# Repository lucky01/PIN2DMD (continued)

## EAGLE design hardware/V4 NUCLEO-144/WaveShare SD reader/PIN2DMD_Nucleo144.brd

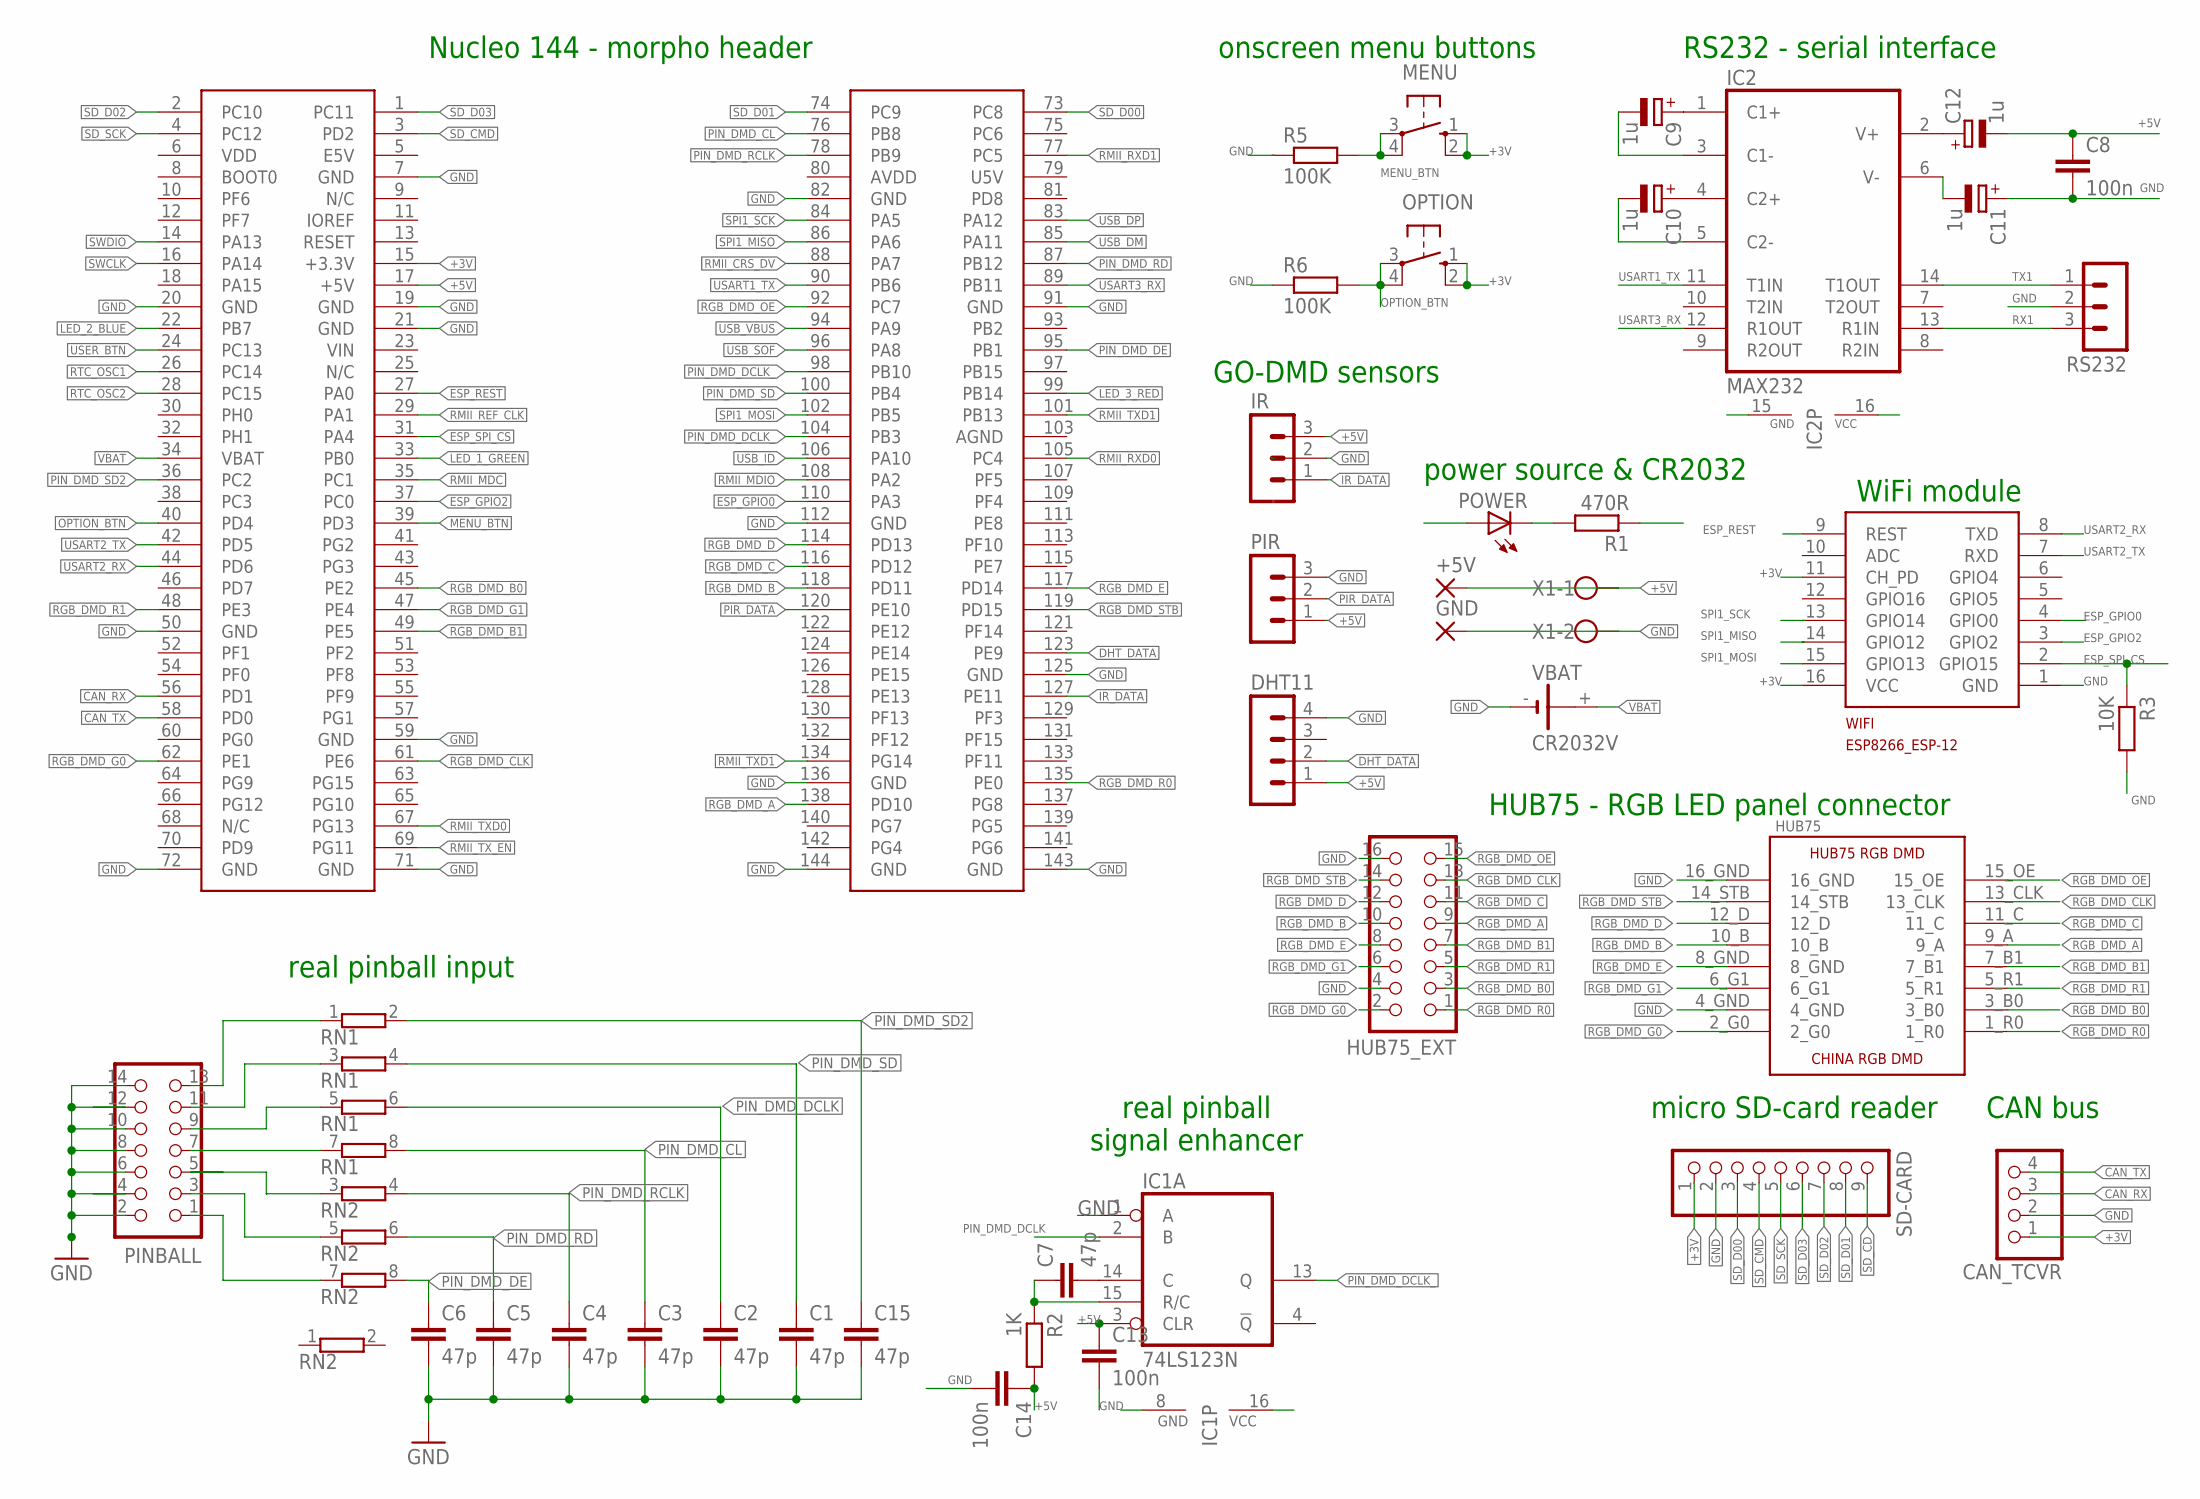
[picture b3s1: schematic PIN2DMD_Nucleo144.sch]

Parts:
+5V: WIREPADSMD2,54-5,08; SMD2,54-5,08
C1, C2, C3, C4, C5, C6, C7, C15: 47p; C025-024X044
C8, C13, C14: 100n; C025-024X044
C9, C10, C11, C12: 1u; E2-4
CAN_TCVR: PINHD-1X4; 1X04
DHT11: MA04-1
GND: WIREPADSMD2,54-5,08; SMD2,54-5,08
HUB75: RGB_DMD_HUB75_HEADER_FEMALE; 16_PIN_HUB75_RGB_FEMALE_DOWN
HUB75_EXT: CON_HEADER_2X08B; PINSHRD_PTH_2X08
IC1: 74LS123N; DIL16
IC2: MAX232; DIL16
IR: MA03-1
MENU: 10-XX; B3F-10XX
OPTION: 10-XX; B3F-10XX
PINBALL: CON_HEADER_2X07-PTH-SHROUDED; PINSHRD_PTH_2X07
PIR: MA03-1
POWER: LED3MM
R1: 470R; 0207/10
R2: 1K; 0207/10
R3: 10K; 0207/10
R5, R6: 100K; 0207/10
RN1, RN2: E4RP; SIL8
RS232: MA03-1
SD-CARD: PINHD-1X9; 1X09
U$1: NUCLEO-144
VBAT: CR2032V
WIFI: ESP8266_ESP-12; ESP8266-ESP12
X1: W237-102

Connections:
+3V: CAN_TCVR.1, MENU.1 (S), MENU.2 (S1), OPTION.1 (S), OPTION.2 (S1), SD-CARD.1, U$1.15 (+3.3V), WIFI.11 (CH_PD), WIFI.16 (VCC)
+5V: +5V.1, C8.1, C12.-, C13.1, C14.1, DHT11.1, IC1.3 (CLR), IC1.16 (VCC), IC2.16 (VCC), IR.3, PIR.1, POWER.A, R2.2, U$1.17 (+5V), X1.1
CAN_RX: CAN_TCVR.3, U$1.56 (PD1)
CAN_TX: CAN_TCVR.4, U$1.58 (PD0)
DHT_DATA: DHT11.2, U$1.123 (PE9)
ESP_GPIO0: U$1.110 (PA3), WIFI.4 (GPIO0)
ESP_GPIO2: U$1.37 (PC0), WIFI.3 (GPIO2)
ESP_REST: U$1.27 (PA0), WIFI.9 (REST)
ESP_SPI_CS: R3.1, U$1.31 (PA4), WIFI.2 (GPIO15)
GND: C1.2, C2.2, C3.2, C4.2, C5.2, C6.2, C8.2, C11.+, C13.2, C14.2, C15.2, CAN_TCVR.2, DHT11.4, GND.1, HUB75.4_GND, HUB75.16_GND, HUB75_EXT.4, HUB75_EXT.16, IC1.1 (A), IC1.8 (GND), IC2.15 (GND), IR.2, PINBALL.2, PINBALL.4, PINBALL.6, PINBALL.8, PINBALL.10, PINBALL.12, PINBALL.14, PIR.3, R1.1, R3.2, R5.1, R6.1, RS232.2, SD-CARD.2, U$1.7 (GND), U$1.19 (GND), U$1.20 (GND), U$1.21 (GND), U$1.50 (GND), U$1.59 (GND), U$1.71 (GND), U$1.72 (GND), U$1.82 (GND), U$1.91 (GND), U$1.112 (GND), U$1.125 (GND), U$1.136 (GND), U$1.143 (GND), U$1.144 (GND), VBAT.-, WIFI.1 (GND), X1.2
IR_DATA: IR.1, U$1.127 (PE11)
LED_1_GREEN: U$1.33 (PB0)
LED_2_BLUE: U$1.22 (PB7)
LED_3_RED: U$1.99 (PB14)
MENU_BTN: MENU.3, MENU.4 (P1), R5.2, U$1.39 (PD3)
unnamed: POWER.K (C), R1.2
unnamed: C7.1, IC1.15 (R/C), R2.1
unnamed: C7.2, IC1.14 (C)
unnamed: C9.+, IC2.1 (C1+)
unnamed: PINBALL.7, RN1.7 (1)
unnamed: PINBALL.5, RN2.3 (1)
unnamed: C10.+, IC2.4 (C2+)
unnamed: C11.-, IC2.6 (V-)
unnamed: C9.-, IC2.3 (C1-)
unnamed: C10.-, IC2.5 (C2-)
unnamed: PINBALL.3, RN2.5 (1)
unnamed: PINBALL.1, RN2.7 (1)
unnamed: PINBALL.9, RN1.5 (1)
unnamed: PINBALL.11, RN1.3 (1)
unnamed: C12.+, IC2.2 (V+)
unnamed: PINBALL.13, RN1.1
OPTION_BTN: OPTION.3, OPTION.4 (P1), R6.2, U$1.40 (PD4)
PIN_DMD_CL: C3.1, RN1.8 (2), U$1.76 (PB8)
PIN_DMD_DCLK: C2.1, IC1.2 (B), RN1.6 (2)
PIN_DMD_DCLK_: IC1.13 (Q), U$1.98 (PB10), U$1.104 (PB3)
PIN_DMD_DE: C6.1, RN2.8 (2), U$1.95 (PB1)
PIN_DMD_RCLK: C4.1, RN2.4 (2), U$1.78 (PB9)
PIN_DMD_RD: C5.1, RN2.6 (2), U$1.87 (PB12)
PIN_DMD_SD: C1.1, RN1.4 (2), U$1.100 (PB4)
PIN_DMD_SD2: C15.1, RN1.2, U$1.36 (PC2)
PIR_DATA: PIR.2, U$1.120 (PE10)
RGB_DMD_A: HUB75.9_A, HUB75_EXT.9, U$1.138 (PD10)
RGB_DMD_B: HUB75.10_B, HUB75_EXT.10, U$1.118 (PD11)
RGB_DMD_B0: HUB75.3_B0, HUB75_EXT.3, U$1.45 (PE2)
RGB_DMD_B1: HUB75.7_B1, HUB75_EXT.7, U$1.49 (PE5)
RGB_DMD_C: HUB75.11_C, HUB75_EXT.11, U$1.116 (PD12)
RGB_DMD_CLK: HUB75.13_CLK, HUB75_EXT.13, U$1.61 (PE6)
RGB_DMD_D: HUB75.12_D, HUB75_EXT.12, U$1.114 (PD13)
RGB_DMD_E: HUB75.8_GND, HUB75_EXT.8, U$1.117 (PD14)
RGB_DMD_G0: HUB75.2_G0, HUB75_EXT.2, U$1.62 (PE1)
RGB_DMD_G1: HUB75.6_G1, HUB75_EXT.6, U$1.47 (PE4)
RGB_DMD_OE: HUB75.15_OE, HUB75_EXT.15, U$1.92 (PC7)
RGB_DMD_R0: HUB75.1_R0, HUB75_EXT.1, U$1.135 (PE0)
RGB_DMD_R1: HUB75.5_R1, HUB75_EXT.5, U$1.48 (PE3)
RGB_DMD_STB: HUB75.14_STB, HUB75_EXT.14, U$1.119 (PD15)
RMII_CRS_DV: U$1.88 (PA7)
RMII_MDC: U$1.35 (PC1)
RMII_MDIO: U$1.108 (PA2)
RMII_REF_CLK: U$1.29 (PA1)
RMII_RXD0: U$1.105 (PC4)
RMII_RXD1: U$1.77 (PC5)
RMII_TXD0: U$1.67 (PG13)
RMII_TXD1: U$1.101 (PB13), U$1.134 (PG14)
RMII_TX_EN: U$1.69 (PG11)
RTC_OSC1: U$1.26 (PC14)
RTC_OSC2: U$1.28 (PC15)
RX1: IC2.13 (R1IN), RS232.3
SD_CD: SD-CARD.9
SD_CMD: SD-CARD.4, U$1.3 (PD2)
SD_D00: SD-CARD.3, U$1.73 (PC8)
SD_D01: SD-CARD.8, U$1.74 (PC9)
SD_D02: SD-CARD.7, U$1.2 (PC10)
SD_D03: SD-CARD.6, U$1.1 (PC11)
SD_SCK: SD-CARD.5, U$1.4 (PC12)
SPI1_MISO: U$1.86 (PA6), WIFI.14 (GPIO12)
SPI1_MOSI: U$1.102 (PB5), WIFI.15 (GPIO13)
SPI1_SCK: U$1.84 (PA5), WIFI.13 (GPIO14)
SWCLK: U$1.16 (PA14)
SWDIO: U$1.14 (PA13)
TX1: IC2.14 (T1OUT), RS232.1
USART1_TX: IC2.11 (T1IN), U$1.90 (PB6)
USART2_RX: U$1.44 (PD6), WIFI.8 (TXD)
USART2_TX: U$1.42 (PD5), WIFI.7 (RXD)
USART3_RX: IC2.12 (R1OUT), U$1.89 (PB11)
USB_DM: U$1.85 (PA11)
USB_DP: U$1.83 (PA12)
USB_ID: U$1.106 (PA10)
USB_SOF: U$1.96 (PA8)
USB_VBUS: U$1.94 (PA9)
USER_BTN: U$1.24 (PC13)
VBAT: U$1.34 (VBAT), VBAT.+

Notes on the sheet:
power source & CR2032
onscreen menu buttons
WiFi module
Nucleo 144 - morpho header
HUB75 - RGB LED panel connector
RS232 - serial interface
GO-DMD sensors
CAN bus
micro SD-card reader
real pinball input
real pinball signal enhancer

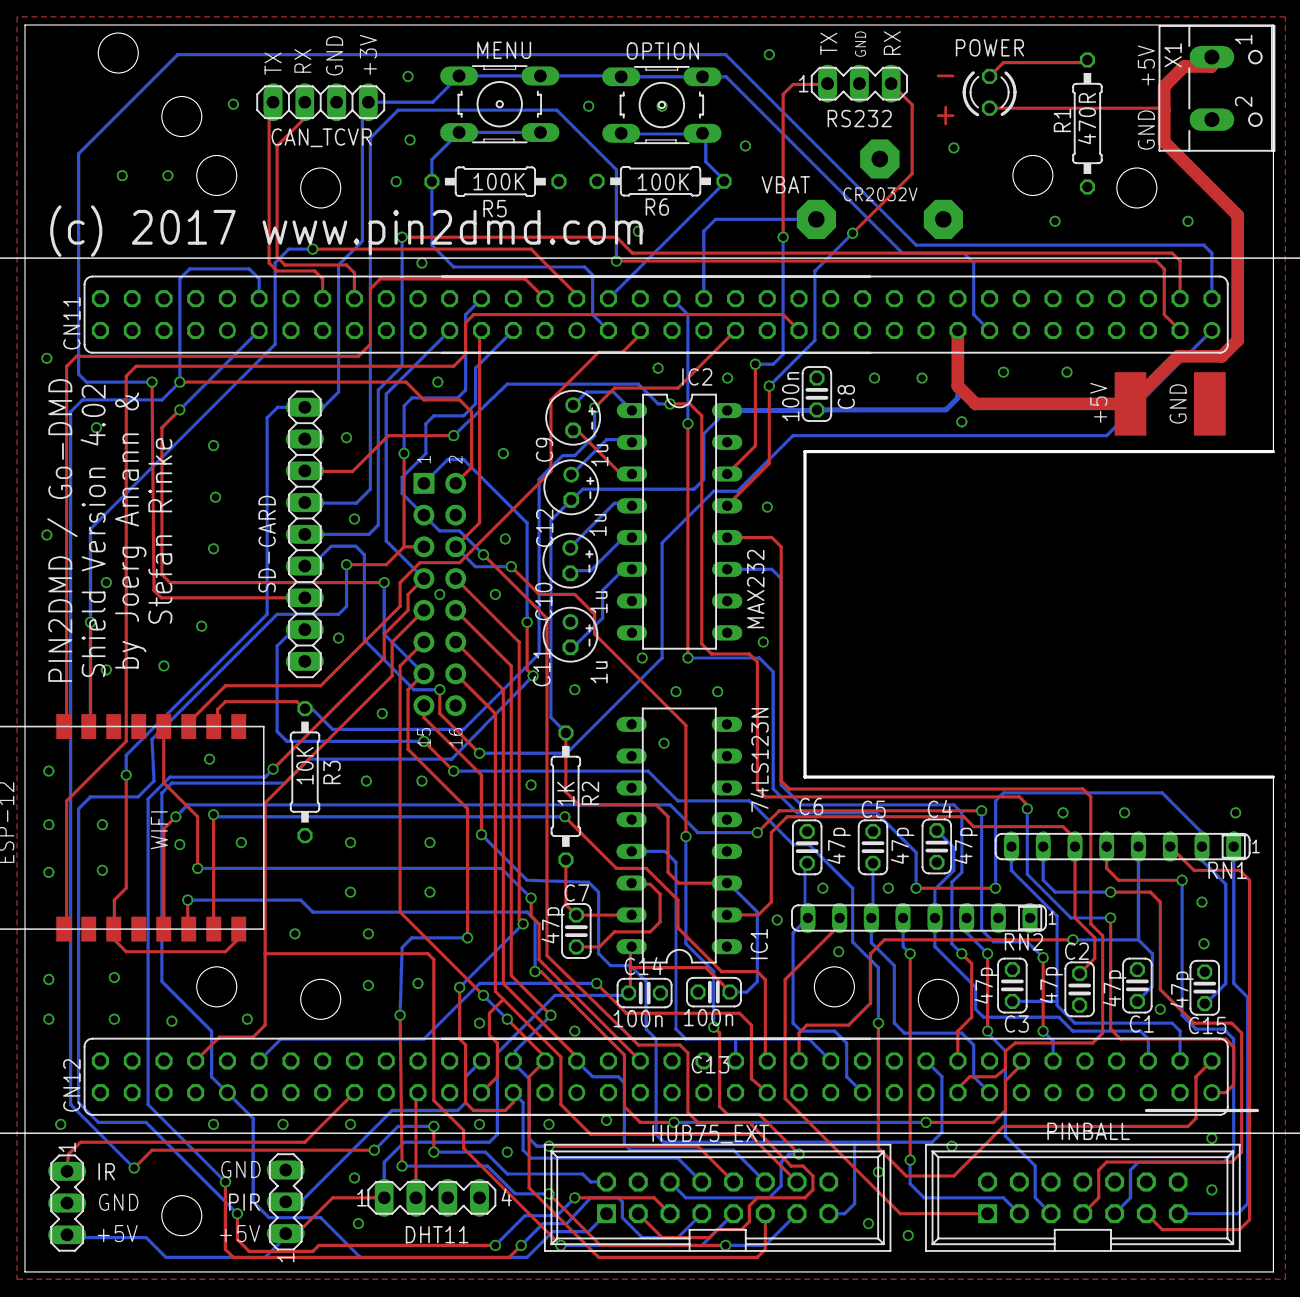
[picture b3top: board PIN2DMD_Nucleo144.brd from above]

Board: 2 copper layers, 99.9 x 99.7 mm, 42 parts (1 on the bottom side), 69 nets.

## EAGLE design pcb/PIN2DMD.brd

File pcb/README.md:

# PIN2DMD - STM32F407VGT6 connector shield

Connector shield for a STM32F4 discovery board to connect a HUB75,
dot matrix display panel.

Optimized by DIY Sascha

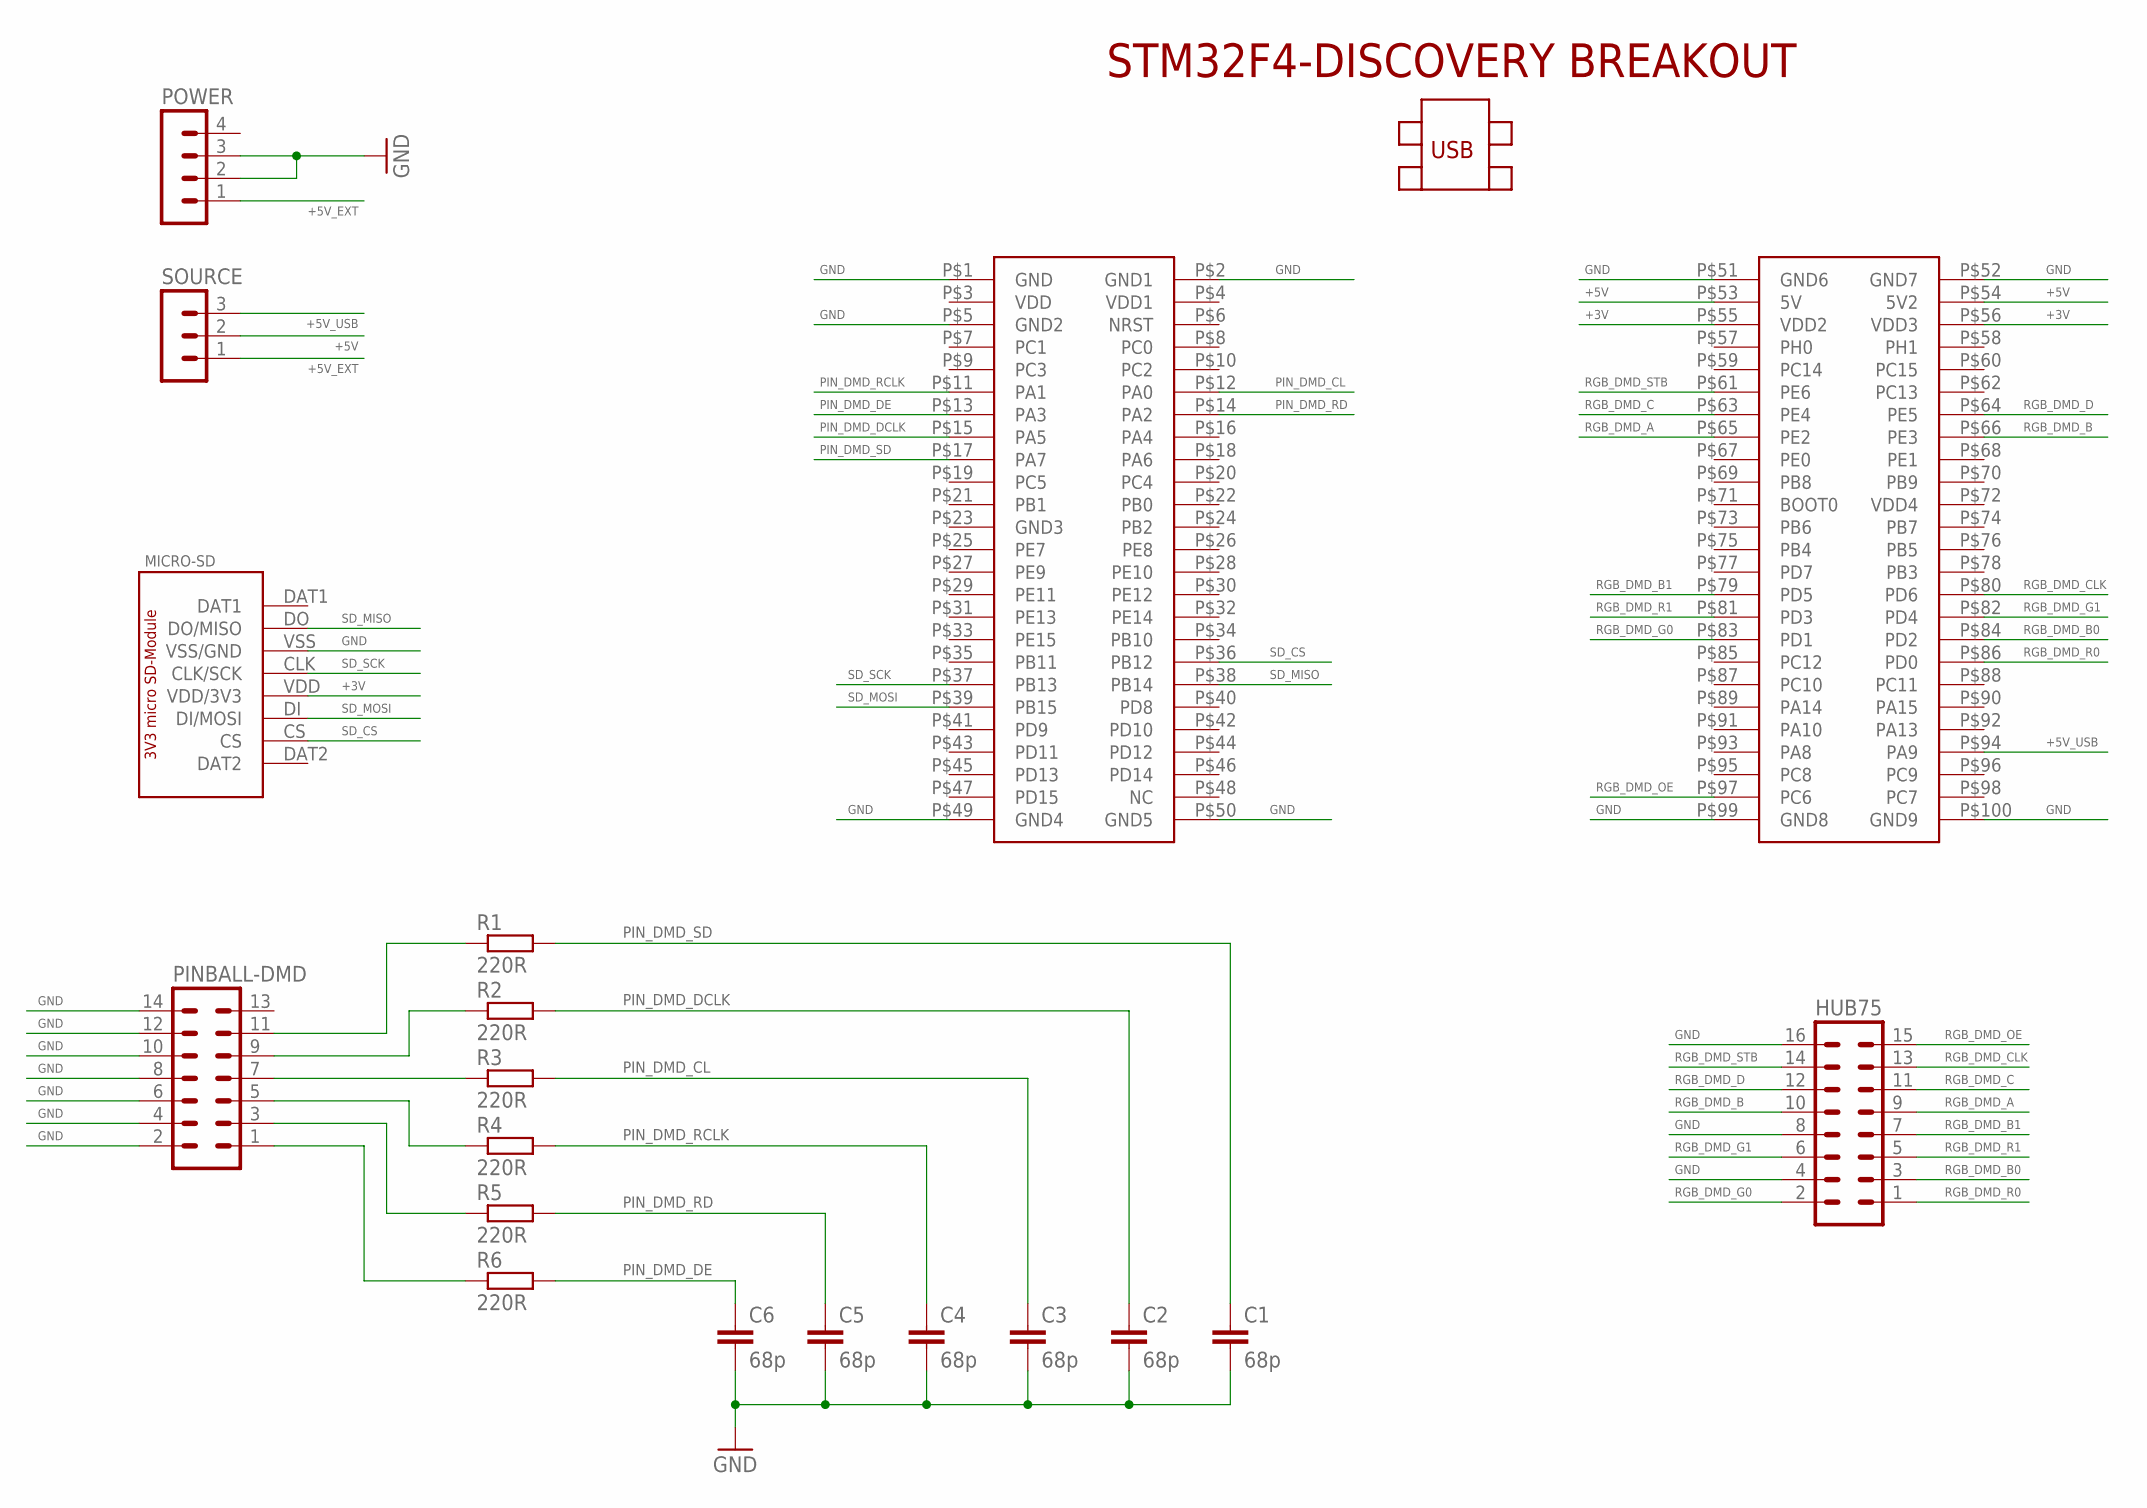
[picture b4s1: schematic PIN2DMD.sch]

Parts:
C1, C2, C3, C4, C5, C6: 68p; C025-024X044
HUB75: MA08-2
MICRO-SD: SPI_SDCARD_3V3_MICRO
PINBALL-DMD: MA07-2
POWER: MA04-1
R1, R2, R3, R4, R5, R6: 220R; 0207/10
SOURCE: MA03-1
U$1: STM32F4-DISCOVERY

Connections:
+3V: MICRO-SD.VDD (VDD/3V3), U$1.P$55 (VDD2), U$1.P$56 (VDD3)
+5V: SOURCE.2, U$1.P$53 (5V), U$1.P$54 (5V2)
+5V_EXT: POWER.1, SOURCE.1
+5V_USB: SOURCE.3, U$1.P$94 (PA9)
GND: C1.2, C2.2, C3.2, C4.2, C5.2, C6.2, HUB75.4, HUB75.8, HUB75.16, MICRO-SD.VSS (VSS/GND), PINBALL-DMD.2, PINBALL-DMD.4, PINBALL-DMD.6, PINBALL-DMD.8, PINBALL-DMD.10, PINBALL-DMD.12, PINBALL-DMD.14, POWER.2, POWER.3, U$1.P$1 (GND), U$1.P$2 (GND1), U$1.P$5 (GND2), U$1.P$49 (GND4), U$1.P$50 (GND5), U$1.P$51 (GND6), U$1.P$52 (GND7), U$1.P$99 (GND8), U$1.P$100 (GND9)
unnamed: PINBALL-DMD.7, R3.1
unnamed: PINBALL-DMD.5, R4.1
unnamed: PINBALL-DMD.3, R5.1
unnamed: PINBALL-DMD.1, R6.1
unnamed: PINBALL-DMD.9, R2.1
unnamed: PINBALL-DMD.11, R1.1
PIN_DMD_CL: C3.1, R3.2, U$1.P$12 (PA0)
PIN_DMD_DCLK: C2.1, R2.2, U$1.P$15 (PA5)
PIN_DMD_DE: C6.1, R6.2, U$1.P$13 (PA3)
PIN_DMD_RCLK: C4.1, R4.2, U$1.P$11 (PA1)
PIN_DMD_RD: C5.1, R5.2, U$1.P$14 (PA2)
PIN_DMD_SD: C1.1, R1.2, U$1.P$17 (PA7)
RGB_DMD_A: HUB75.9, U$1.P$65 (PE2)
RGB_DMD_B: HUB75.10, U$1.P$66 (PE3)
RGB_DMD_B0: HUB75.3, U$1.P$84 (PD2)
RGB_DMD_B1: HUB75.7, U$1.P$79 (PD5)
RGB_DMD_C: HUB75.11, U$1.P$63 (PE4)
RGB_DMD_CLK: HUB75.13, U$1.P$80 (PD6)
RGB_DMD_D: HUB75.12, U$1.P$64 (PE5)
RGB_DMD_G0: HUB75.2, U$1.P$83 (PD1)
RGB_DMD_G1: HUB75.6, U$1.P$82 (PD4)
RGB_DMD_OE: HUB75.15, U$1.P$97 (PC6)
RGB_DMD_R0: HUB75.1, U$1.P$86 (PD0)
RGB_DMD_R1: HUB75.5, U$1.P$81 (PD3)
RGB_DMD_STB: HUB75.14, U$1.P$61 (PE6)
SD_CS: MICRO-SD.CS, U$1.P$36 (PB12)
SD_MISO: MICRO-SD.DO (DO/MISO), U$1.P$38 (PB14)
SD_MOSI: MICRO-SD.DI (DI/MOSI), U$1.P$39 (PB15)
SD_SCK: MICRO-SD.CLK (CLK/SCK), U$1.P$37 (PB13)

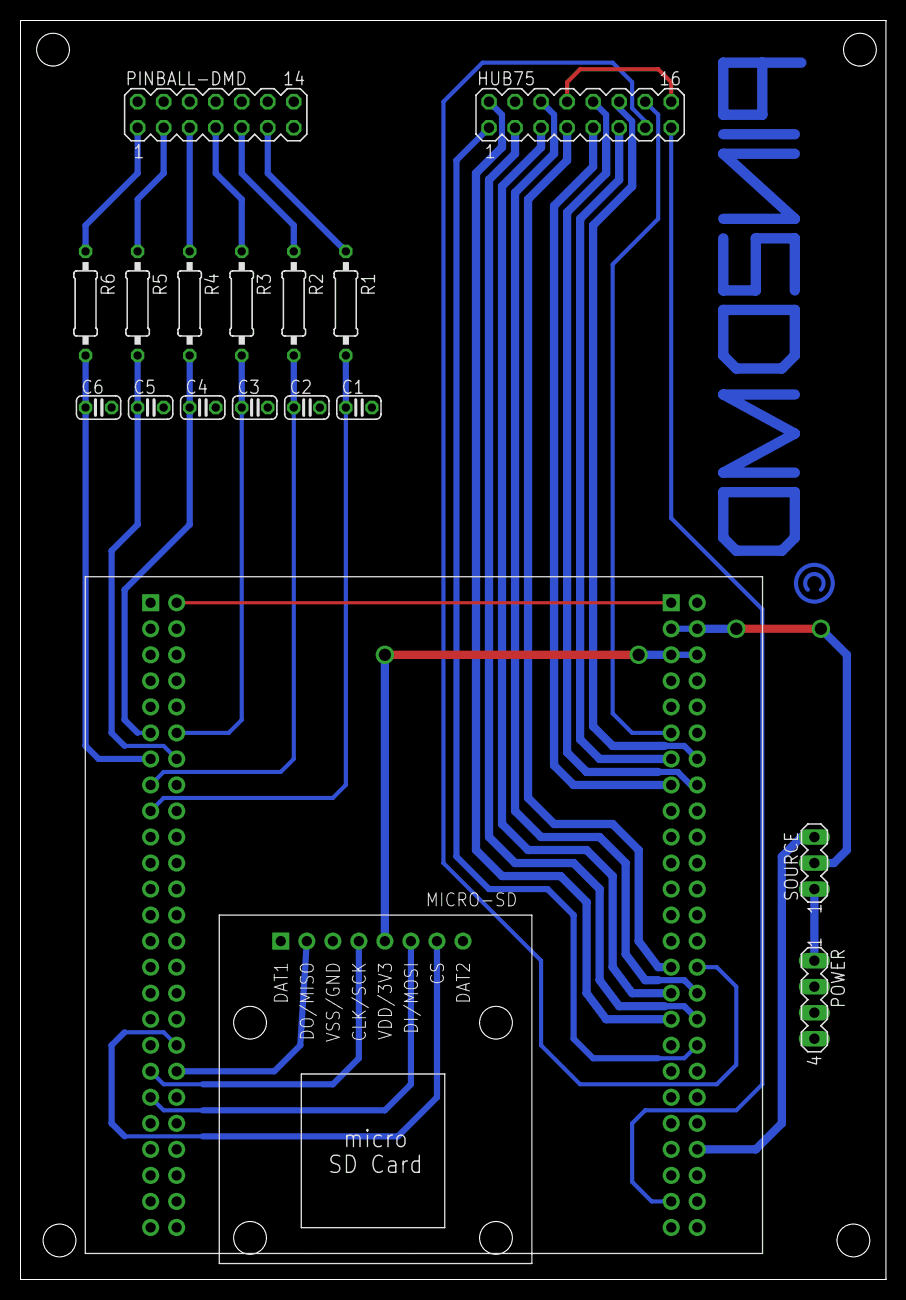
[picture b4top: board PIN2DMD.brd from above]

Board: 2 copper layers, 84.5 x 122.9 mm, 18 parts (0 on the bottom side), 34 nets.
